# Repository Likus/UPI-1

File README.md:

# УПИ-1 — самодельная портативная игровая консоль

*УПИ — **У**стройство **П**ортативное **И**гровое; 1 — первое в серии.*

Прошивки, утилиты разработки, проект платы и 3D-модели корпуса самодельной
ретро-консоли на микроконтроллере **WCH CH32V003** (RISC-V, 48 kB FLASH, 2 kB RAM).

> **Основано на:** [CH32V003-GameConsole](https://github.com/wagiminator/CH32V003-GameConsole) —
> открытой мини-консоли Стефана Вагнера ([wagiminator](https://github.com/wagiminator)).
> Архитектура, базовые драйверы CH32V003 и порты классических игр унаследованы оттуда;
> аппаратная часть и значительная часть прошивок переработаны для УПИ-1.

[English summary](#english-summary)

## Характеристики консоли

| Параметр      | Значение                                             |
|---------------|------------------------------------------------------|
| МК            | CH32V003A4M6 (TSSOP20) @ 12 МГц (HSI)              |
| Экран         | OLED 128×64, SSD1306, I2C (bit-bang, SDA=PC1, SCL=PC2)|
| Звук          | активный звукоизлучатель на PC0                      |
| Управление    | D-pad: UP=PC3, LEFT=PC4, DOWN=PC6, RIGHT=PC7; ACT1=PD4, ACT2=PD5 |
| Питание       | батарейное (см. раздел «Аппаратная часть»)           |

## Структура репозитория

```
firmware/     — прошивки (каждый проект = отдельный PlatformIO-проект)
tools/        — браузерные утилиты разработки и палитры для редактора карт
hardware/     — проект основной платы (KiCad)
enclosure/    — 3D-модели корпуса (конфигурации k1–k3)
```

## Прошивки (`firmware/`)

| Проект                  | Описание | Происхождение |
|-------------------------|----------|---------------|
| `template`              | Шаблон для новых игр: кнопки, звук, отрисовка | свой код на базе шаблонов wagiminator |
| `tiny-tris`             | «Тетрис» | Tiny Tris (Daniel C), CH32V003-порт wagiminator, адаптирован |
| `tiny-invaders`         | «Космические захватчики» | Tiny Invaders (Daniel C), CH32V003-порт wagiminator, адаптирован |
| `tiny-arkanoid`         | «Арканоид» | Tiny Arkanoid (Daniel C), CH32V003-порт wagiminator, адаптирован |
| `snake`                 | «Змейка» | порт игры Terrabyte (Dmitriy Stukalov) |
| `maze`                  | Лабиринт, 20 уровней зашиты в ресурсы | своя игра |
| `sever-race-mini`       | Гонки с сохранением рекорда во FLASH | своя игра |
| `tanks`                 | Танковые бои по карте 24×16 | своя игра |
| `dupi`                  | Raycaster-шутер от первого лица (fixed-point) | своя игра |

Общая часть своих игр — `engine.h` (API консоли `UPI_*`) и `draw.c/h`
(фреймбуфер 128×64 поверх SSD1306-драйвера `oled.c`).

## Сборка и прошивка

Каждая папка в `firmware/` — самостоятельный [PlatformIO](https://platformio.org)-проект.

1. Установьте PlatformIO Core или расширение PlatformIO IDE для VS Code.
2. Платформа `CH32V` подтянется автоматически (используется
   [community platform-ch32v](https://github.com/Community-PIO-CH32V/platform-ch32v),
   плата `genericCH32V003A4M6`).
3. Сборка: откройте папку проекта и выполните `pio run`.
4. Прошивка: `pio run -t upload` — через WCH-Link (`upload_protocol = wch-link`)
   либо другим способом по UART, настроив `upload_port`/`upload_protocol`.

Часть проектов дополнительно содержит `makefile` для сборки без PlatformIO.

Предупреждение: прошивка CH32V003 «съедает» сброс в режим WCH-Link по умолчанию —
для перепрошивки может потребоваться утилита WCHISPTool или режим Force.

## Утилиты (`tools/`)

Открываются в любом браузере, интернет не нужен:

- **img4upi.html** — конвертер картинок в монохромные битмапы для прошивок;
- **map4XxX.html** — редактор тайловых карт (палитры из `tools/palettes/`:
  `25x25.json`, `tanks.json`, `dupi.json`);
- **music4upi.html** — редактор частотных последовательностей для звукоизлучателя.

## Аппаратная часть

Проект основной платы — в `hardware/` (KiCad): схема, трассировка,
инструкции по экспорту производственных файлов. 3D-модели корпуса — в `enclosure/`:
три конфигурации (k1 — девелоперская с разъёмом программирования, k2 — стандартная,
k3 — special edition без логотипа), подробнее в `enclosure/README.md`.

## Третьи авторы

- **Стефан Вагнер ([wagiminator](https://github.com/wagiminator))** — источник всего
  фундамента проекта: его [CH32V003-GameConsole](https://github.com/wagiminator/CH32V003-GameConsole)
  дал УПИ-1 архитектуру, базовые драйверы (`system.h`, `gpio.h`, `i2c_tx.*`,
  `ch32v003.h`, `driver.h`, `oled_term.*`, `millis.*`, `flash.*`, CC BY-SA 3.0) и
  CH32V003-конверсии классических игр.
- **Daniel C ([TinyGamePad](https://www.tinyjoypad.com))** — оригиналы Tiny Tris /
  Tiny Invaders / Tiny Arkanoid (GPLv3).
- **Dmitriy Stukalov (Terrabyte)** — порт «Змейки» на шаблонах wagiminator.

## Контакты

Telegram: [@likus_workshop](https://t.me/likus_workshop) · VK: [vk.ru/likusworkshop](https://vk.ru/likusworkshop)

## Лицензия

Репозиторий публикуется под **GNU GPL v3** (или новее) — см. [LICENSE](LICENSE).
Файлы сторонних авторов сохраняют свои исходные лицензии и указанны в шапках;
детали — в разделе «Третьи авторы».

---

## English summary

**UPI-1** (from Russian «Устройство Портативное Игровое» — *portable gaming
device*, unit 1) is a personal DIY handheld game console project. **It is based
on [CH32V003-GameConsole](https://github.com/wagiminator/CH32V003-GameConsole)
by Stefan Wagner ([wagiminator](https://github.com/wagiminator))** — the console
architecture, the base CH32V003 drivers and the classic-game conversions are
inherited from it, while the hardware and much of the firmware were reworked.
The console is built around the WCH CH32V003 RISC-V MCU with a 128×64 SSD1306
OLED display, an active buzzer and six GPIO buttons. This repository holds the
firmware (PlatformIO projects: classic game ports and original games — a maze,
a racing game with FLASH high-score storage, tanks and a fixed-point
raycaster), browser-based development tools (image/map/sound converters), the
KiCad board project and printable enclosure models (three configurations). See
the Russian text above for details. Licensed under GPLv3; third-party files
keep their original licenses (CC BY-SA 3.0 by wagiminator, GPLv3 TinyGamePad
games by Daniel C).

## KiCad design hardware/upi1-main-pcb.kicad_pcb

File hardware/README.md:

# Плата консоли УПИ-1

Проект основной печатной платы в KiCad (создан в KiCad 10).

Файлы:

- `upi1-main-pcb.kicad_pro` — проект;
- `upi1-main-pcb.kicad_sch` — схема (U2 — CH32V003A4M6);
- `upi1-main-pcb.kicad_pcb` — трассированная плата.

Библиотеки встроены в файлы проекта — внешних зависимостей нет, достаточно
открыть `.kicad_pro` в KiCad 9/10.

## Производство

Gerber-файлы, сверловка и прочее не хранятся в репозитории — они воспроизводятся
экспортом из KiCad:

- Gerber: *Файл → Изготовить → Экспортировать Gerber…* (включая Edge_Cuts);
- сверловка: *Excellon* из того же диалога;
- BOM/позиционный файл: плагин *Export* / *Позиционные файлы*.

Опубликованные автором партии плат изготовлены по состоянию этого проекта.

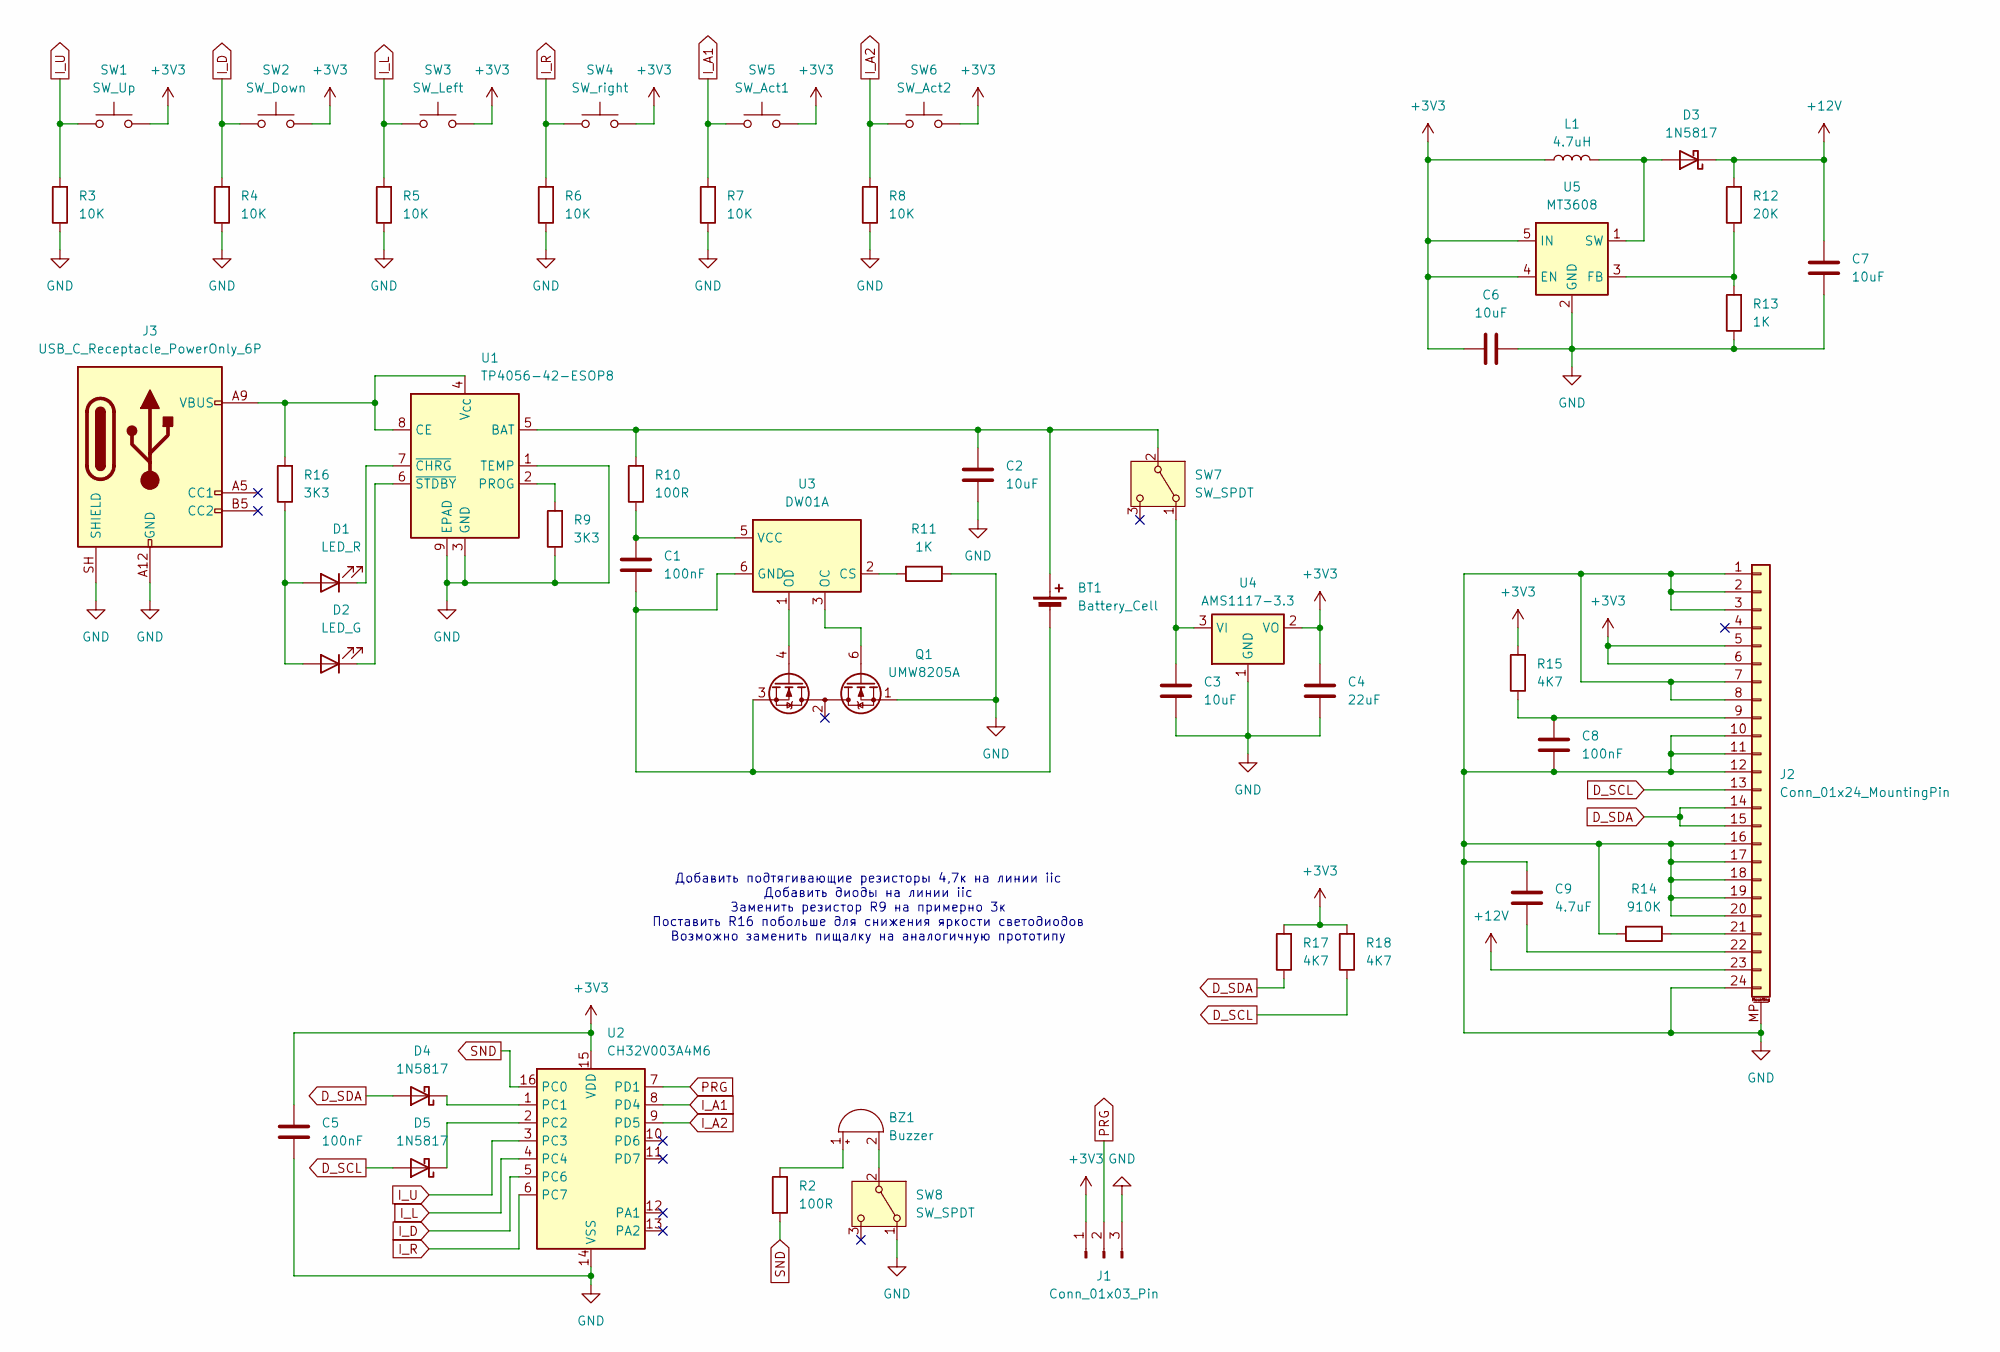
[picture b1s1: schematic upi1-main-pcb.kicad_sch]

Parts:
BT1: Battery_Cell; PinSocket_1x02_P2.54mm_Vertical
BZ1: Buzzer; Buzzer_TDK_PS1240P02BT_D12.2mm_H6.5mm
C1, C5, C8: 100nF; C_0805_2012Metric_Pad1.18x1.45mm_HandSolder
C2, C3, C6, C7: 10uF; C_0805_2012Metric_Pad1.18x1.45mm_HandSolder
C4: 22uF; C_0805_2012Metric_Pad1.18x1.45mm_HandSolder
C9: 4.7uF; C_0805_2012Metric_Pad1.18x1.45mm_HandSolder
D1: LED_R; LED_0805_2012Metric_Pad1.15x1.40mm_HandSolder
D2: LED_G; LED_0805_2012Metric_Pad1.15x1.40mm_HandSolder
D3, D4, D5: 1N5817; D_SOD-123
J1: Conn_01x03_Pin; PinHeader_1x03_P2.54mm_Vertical
J2: Conn_01x24_MountingPin; Hirose_FH12-24S-0.5SH_1x24-1MP_P0.50mm_Horizontal
J3: USB_C_Receptacle_PowerOnly_6P; USB_C_Receptacle_GCT_USB4125-xx-x-0190_6P_TopMnt_Horizontal
L1: 4.7uH; L_0805_2012Metric_Pad1.05x1.20mm_HandSolder
Q1: UMW8205A; SOT-23-6_Handsoldering
R2, R10: 100R; R_0805_2012Metric_Pad1.20x1.40mm_HandSolder
R3, R4, R5, R6, R7, R8: 10K; R_0805_2012Metric_Pad1.20x1.40mm_HandSolder
R9, R16: 3K3; R_0805_2012Metric_Pad1.20x1.40mm_HandSolder
R11: 1K; R_0805_2012Metric_Pad1.20x1.40mm_HandSolder
R12: 20К; R_0805_2012Metric_Pad1.20x1.40mm_HandSolder
R13: 1К; R_0805_2012Metric_Pad1.20x1.40mm_HandSolder
R14: 910К; R_0805_2012Metric_Pad1.20x1.40mm_HandSolder
R15, R17, R18: 4K7; R_0805_2012Metric_Pad1.20x1.40mm_HandSolder
SW1: SW_Up; SW_Push_1TS009xxxx-xxxx-xxxx_6x6x5mm
SW2: SW_Down; SW_Push_1TS009xxxx-xxxx-xxxx_6x6x5mm
SW3: SW_Left; SW_Push_1TS009xxxx-xxxx-xxxx_6x6x5mm
SW4: SW_right; SW_Push_1TS009xxxx-xxxx-xxxx_6x6x5mm
SW5: SW_Act1; SW_Push_1TS009xxxx-xxxx-xxxx_6x6x5mm
SW6: SW_Act2; SW_Push_1TS009xxxx-xxxx-xxxx_6x6x5mm
SW7, SW8: SW_SPDT; SW_Slide_SPDT_Angled_CK_OS102011MA1Q
U1: TP4056-42-ESOP8; SOIC-8-1EP_3.9x4.9mm_P1.27mm_EP2.41x3.3mm_ThermalVias
U2: CH32V003A4M6; STC_SOP-16_3.9x9.9mm_P1.27mm
U3: DW01A; SOT-23-6
U4: AMS1117-3.3; SOT-223-3_TabPin2
U5: MT3608; SOT-23-6

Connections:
+3V3: C4.2, C5.1, C6.2, J1.1, J2.5, J2.6, L1.1, R15.2, R17.2, R18.2, SW1.2, SW2.2, SW3.2, SW4.2, SW5.2, SW6.2, U2.15 (VDD), U4.2 (VO), U5.4 (EN), U5.5 (IN)
+12V: C7.2, D3.1 (K), J2.23, R12.2
D_SCL: D5.2 (A), J2.13, R18.1
D_SDA: D4.2 (A), J2.14, J2.15, R17.1
GND: C2.1, C3.1, C4.1, C5.2, C6.1, C7.1, C8.2, C9.1, J1.3, J2.1, J2.2, J2.3, J2.7, J2.8, J2.10, J2.11, J2.12, J2.16, J2.17, J2.18, J2.19, J2.20, J2.24, J2.MP (MountPin), J3.A12 (GND), J3.B12 (GND), J3.SH (SHIELD), Q1.1 (D1), R3.1, R4.1, R5.1, R6.1, R7.1, R8.1, R9.1, R11.1, R13.1, R14.2, SW8.1 (A), U1.1 (TEMP), U1.3 (GND), U1.9 (EPAD), U2.14 (VSS), U4.1 (GND), U5.2 (GND)
I_A1: R7.2, SW5.1, U2.8 (PD4)
I_A2: R8.2, SW6.1, U2.9 (PD5)
I_D: R4.2, SW2.1, U2.5 (PC6)
I_L: R5.2, SW3.1, U2.4 (PC4)
I_R: R6.2, SW4.1, U2.6 (PC7)
I_U: R3.2, SW1.1, U2.3 (PC3)
unnamed: BT1.1 (+), C2.2, R10.2, SW7.2 (B), U1.5 (BAT)
unnamed: BT1.2 (-), C1.2, Q1.3 (S2), U3.6 (GND)
unnamed: BZ1.1 (+), R2.1
unnamed: BZ1.2 (-), SW8.2 (B)
unnamed: D1.2 (A), D2.2 (A), R16.1
unnamed: D1.1 (K), U1.7 (~CHRG)
unnamed: D2.1 (K), U1.6 (~STDBY)
unnamed: D3.2 (A), L1.2, U5.1 (SW)
unnamed: D4.1 (K), U2.1 (PC1)
unnamed: D5.1 (K), U2.2 (PC2)
unnamed: C8.1, J2.9, R15.1
unnamed: J2.21, R14.1
unnamed: C9.2, J2.22
unnamed: Q1.6 (G1), U3.3 (OC)
unnamed: Q1.4 (G2), U3.1 (OD)
unnamed: C3.2, SW7.1 (A), U4.3 (VI)
unnamed: J3.A9 (VBUS), J3.B9 (VBUS), R16.2, U1.4 (V_{CC}), U1.8 (CE)
unnamed: R9.2, U1.2 (PROG)
unnamed: R11.2, U3.2 (CS)
unnamed: C1.1, R10.1, U3.5 (VCC)
unnamed: R12.1, R13.2, U5.3 (FB)
PRG: J1.2, U2.7 (PD1)
SND: R2.2, U2.16 (PC0)

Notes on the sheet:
Добавить подтягивающие резисторы 4,7к на линии iic Добавить диоды на линии iic Заменить резистор R9 на примерно 3к Поставить R16 побольше для снижения яркости светодиодов Возможно заменить пищалку на аналогичную прототипу

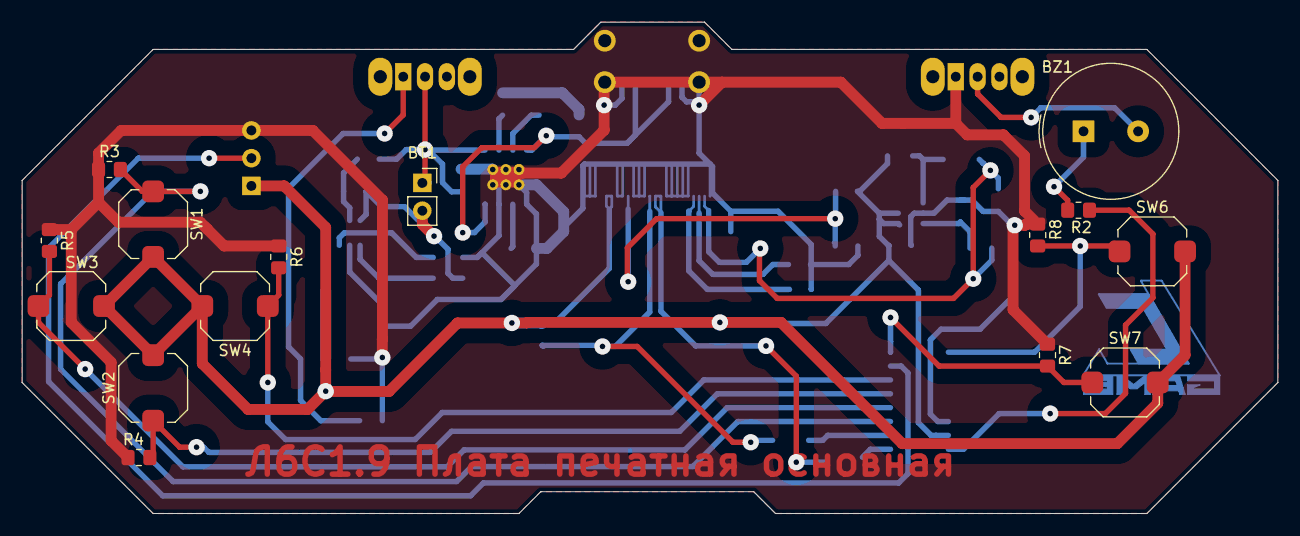
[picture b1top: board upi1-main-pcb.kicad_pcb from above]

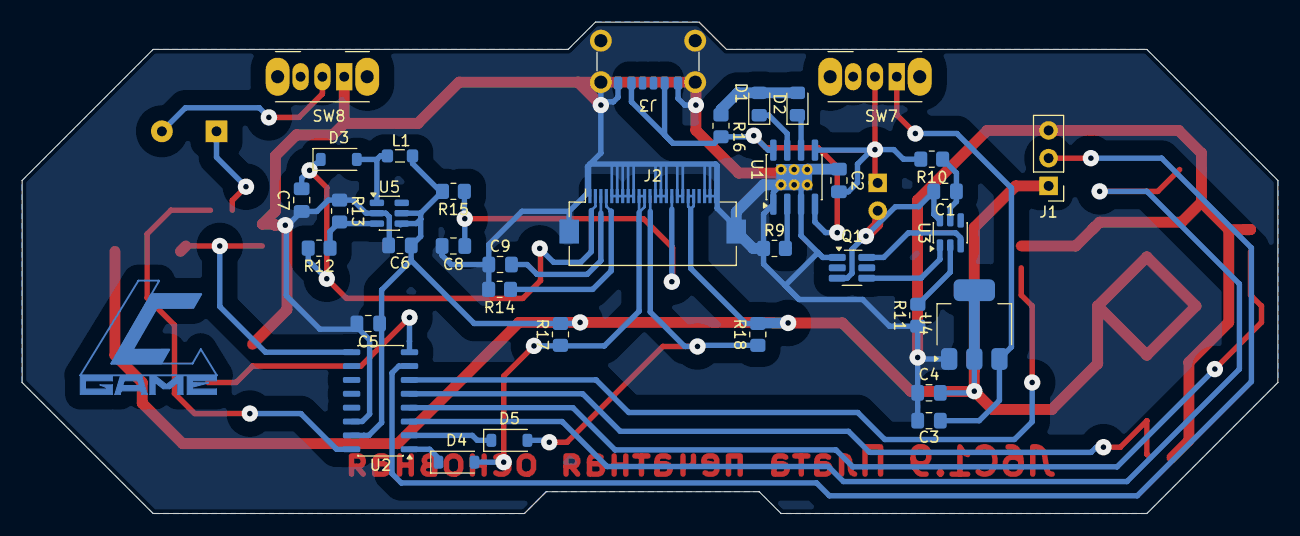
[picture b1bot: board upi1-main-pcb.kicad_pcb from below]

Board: 2 copper layers, 115.0 x 45.0 mm, 51 parts (36 on the bottom side), 34 nets.

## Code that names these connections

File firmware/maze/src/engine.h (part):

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#include "draw.h"

// Pin assignments
#define PIN_BEEP    PC0   // pin connected to buzzer
#define PIN_SCL     PC2   // pin connected to OLED (I2C SCL)
#define PIN_SDA     PC1   // pin connected to OLED (I2C SDA)

#define PIN_BTN_UP  PC3
#define PIN_BTN_RG  PC7
#define PIN_BTN_DW  PC6
#define PIN_BTN_LF  PC4
#define PIN_BTN_ACT1  PD4
#define PIN_BTN_ACT2  PD5

// Joypad calibration values
#define UPI_BTN_UP          168   // joypad UP
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

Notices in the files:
firmware/maze/src/engine.h:
SPDX-License-Identifier: GPL-3.0-or-later
Copyright (C) 2026 Likus - UPI-1 handheld console firmware
